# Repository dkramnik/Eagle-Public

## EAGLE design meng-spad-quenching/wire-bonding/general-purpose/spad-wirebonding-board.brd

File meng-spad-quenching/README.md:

#meng-spad-quenching

This repository contains circuit designs for my M.Eng. project in Professor Rajeev Ram's group at MIT. These circuits are primarily related to quenching single-photon avalanche diodes (SPADs) fabricated in 90nm CMOS through MOSIS. My thesis contains full documentation (dspace link posted when available).

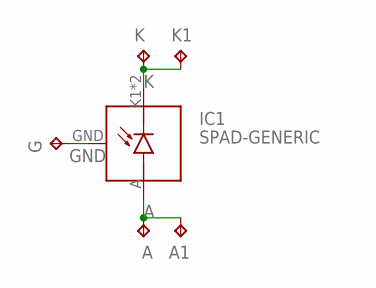
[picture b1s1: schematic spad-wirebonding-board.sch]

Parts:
A, A1: TPTP10R; TP10R
G: TPTP10R; TP10R
IC1: SPAD-GENERIC; SPAD-WIREBOND-GENERIC-CRYO
K, K1: TPTP10R; TP10R

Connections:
A: A.TP, A1.TP, IC1.A (SPAD_ANODE)
GND: G.TP, IC1.GND
K: IC1.K1 (SPAD_CATHODE), IC1.K2 (SPAD_CATHODE), K.TP, K1.TP

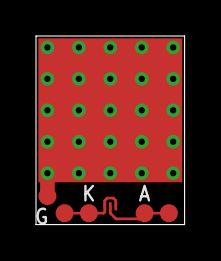
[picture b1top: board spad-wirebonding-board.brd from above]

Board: 2 copper layers, 8.3 x 10.5 mm, 6 parts (0 on the bottom side), 3 nets.

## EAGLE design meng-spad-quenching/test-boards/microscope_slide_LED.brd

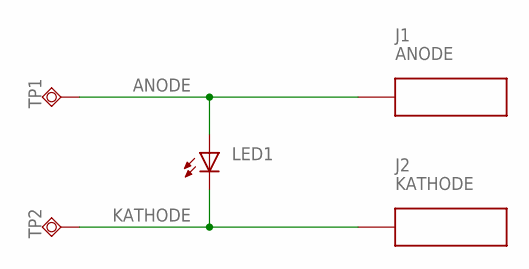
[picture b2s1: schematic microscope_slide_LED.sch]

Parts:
J1: ANODE; 0.125_PAD
J2: KATHODE; 0.125_PAD
LED1: LEDCHIPLED_0603; CHIPLED_0603
TP1: ANODE; TP20SQ
TP2: KATHODE; TP20SQ

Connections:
ANODE: J1.1, LED1.A, TP1.TP
KATHODE: J2.1, LED1.C, TP2.TP

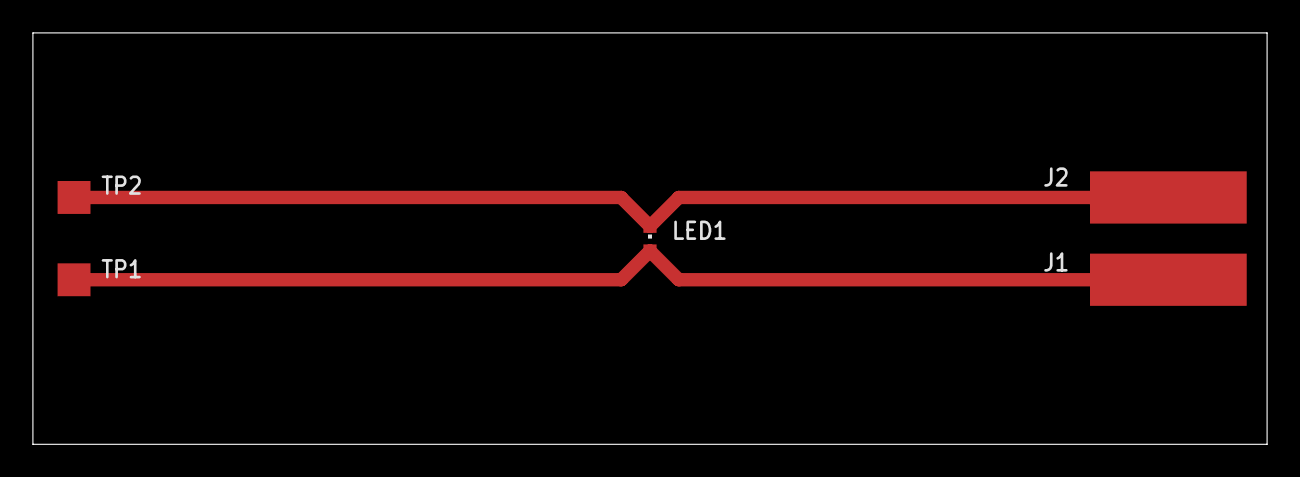
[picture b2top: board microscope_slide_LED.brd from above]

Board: 2 copper layers, 75.0 x 25.0 mm, 5 parts (0 on the bottom side), 2 nets.

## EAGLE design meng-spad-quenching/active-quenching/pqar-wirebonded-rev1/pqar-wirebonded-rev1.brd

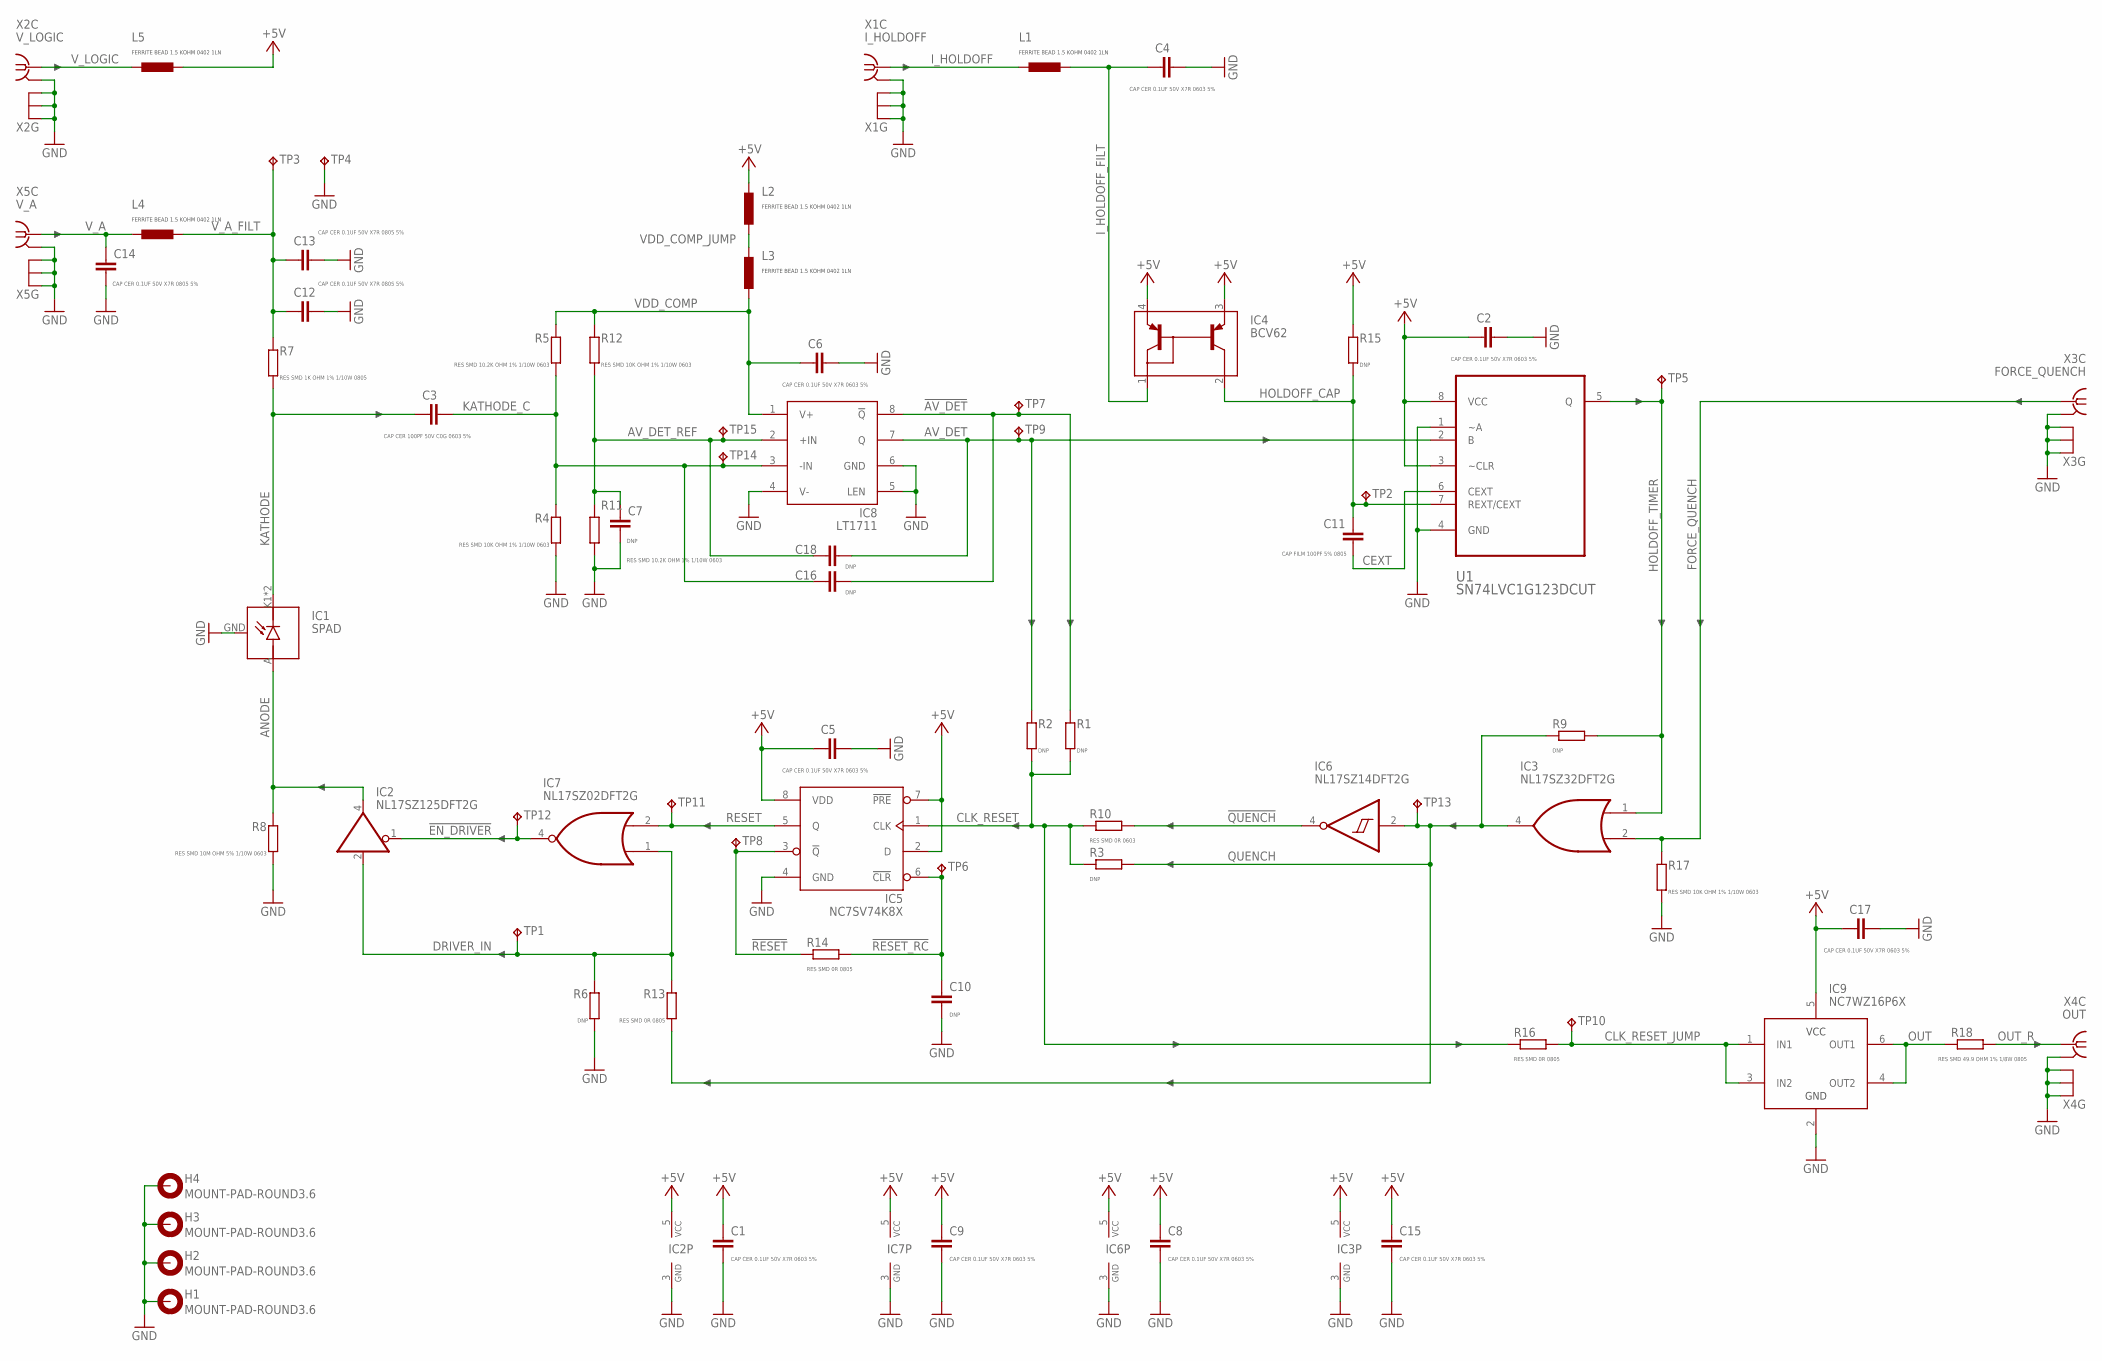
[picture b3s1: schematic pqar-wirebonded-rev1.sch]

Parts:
C1, C2, C4, C5, C6, C8, C9, C15, C17: CAP CER 0.1UF 50V X7R 0603 5%; C0603
C3: CAP CER 100PF 50V C0G 0603 5%; C0603
C7: DNP; C0603
C10, C16, C18: DNP; C0805
C11: CAP FILM 100PF 5% 0805; C0805
C12, C13, C14: CAP CER 0.1UF 50V X7R 0805 5%; C0805
H1, H2, H3, H4: MOUNT-PAD-ROUND3.6; 3,6-PAD
IC1: SPAD; SPAD-WIREBOND-GENERIC-CRYO
IC2: NL17SZ125DFT2G; SC70-5
IC3: NL17SZ32DFT2G; SC70-5
IC4: BCV62; SOT143B
IC5: NC7SV74K8X; US8_3.1MM_JDEC_MO-187
IC6: NL17SZ14DFT2G; SC70-5
IC7: NL17SZ02DFT2G; SC70-5
IC8: LT1711; MSOP8
IC9: NC7WZ16P6X; SC70-6L
L1, L2, L3, L4, L5: FERRITE BEAD 1.5 KOHM 0402 1LN; R0402
R1, R2, R6, R15: DNP; R0805
R3, R9: DNP; R0603
R4, R12, R17: RES SMD 10K OHM 1% 1/10W 0603; R0603
R5, R11: RES SMD 10.2K OHM 1% 1/10W 0603; R0603
R7: RES SMD 1K OHM 1% 1/10W 0805; R0805
R8: RES SMD 10M OHM 5% 1/10W 0603; R0603
R10: RES SMD 0R 0603; R0603
R13, R14, R16: RES SMD 0R 0805; R0805
R18: RES SMD 49.9 OHM 1% 1/8W 0805; R0805
TP1, TP2, TP3, TP4, TP5, TP6, TP7, TP8, TP9, TP10, TP11, TP12, TP13, TP14, TP15: AV_DET; TP10R
U1: SN74LVC1G123DCUT; SOP50P310X90-8N
X1: I_HOLDOFF; MMCX-SMT-BIGPADS
X2: V_LOGIC; MMCX-SMT-BIGPADS
X3: FORCE_QUENCH; MMCX-SMT-BIGPADS
X4: OUT; MMCX-SMT-BIGPADS
X5: V_A; MMCX-SMT-BIGPADS

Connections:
!AV_DET: C16.2, IC8.8 (!Q), R1.1, TP7.TP
!EN_DRIVER: IC2.1 (OE), IC7.4 (O), TP12.TP
!QUENCH: IC6.4 (O), R10.2
!RESET: IC5.3 (!Q), R14.1, TP8.TP
!RESET_RC: C10.1, IC5.6 (!CLR), R14.2, TP6.TP
+5V: C1.1, C2.1, C5.1, C8.1, C9.1, C15.1, C17.1, IC2.5 (VCC), IC3.5 (VCC), IC4.3 (E_OUT), IC4.4 (E_IN), IC5.2 (D), IC5.7 (!PRE), IC5.8 (VDD), IC6.5 (VCC), IC7.5 (VCC), IC9.5 (VCC), L2.1, L5.2, R15.1, U1.3 (~CLR), U1.8 (VCC)
ANODE: IC1.A (SPAD_ANODE), IC2.4 (O), R8.1
AV_DET: C18.2, IC8.7 (Q), R2.1, TP9.TP, U1.2 (B)
AV_DET_REF: C7.1, C18.1, IC8.2 (+IN), R11.1, R12.2, TP15.TP
CEXT: C11.2, U1.6 (CEXT)
CLK_RESET: IC5.1 (CLK), R1.2, R2.2, R3.1, R10.1, R16.1
CLK_RESET_JUMP: IC9.1 (IN1), IC9.3 (IN2), R16.2, TP10.TP
DRIVER_IN: IC2.2 (I), IC7.1 (I0), R6.1, R13.1, TP1.TP
FORCE_QUENCH: IC3.2 (I1), R17.1, X3.S (1)
GND: C1.2, C2.2, C4.2, C5.2, C6.2, C7.2, C8.2, C9.2, C10.2, C12.2, C13.2, C14.2, C15.2, C17.2, H1.B3,6, H2.B3,6, H3.B3,6, H4.B3,6, IC1.GND, IC2.3 (GND), IC3.3 (GND), IC5.4 (GND), IC6.3 (GND), IC7.3 (GND), IC8.4 (V-), IC8.5 (LEN), IC8.6 (GND), IC9.2 (GND), R4.2, R6.2, R8.2, R11.2, R17.2, TP4.TP, U1.1 (~A), U1.4 (GND), X1.G1 (GND), X1.G2 (GND), X1.G3 (GND), X1.G4 (GND), X2.G1 (GND), X2.G2 (GND), X2.G3 (GND), X2.G4 (GND), X3.G1 (GND), X3.G2 (GND), X3.G3 (GND), X3.G4 (GND), X4.G1 (GND), X4.G2 (GND), X4.G3 (GND), X4.G4 (GND), X5.G1 (GND), X5.G2 (GND), X5.G3 (GND), X5.G4 (GND)
HOLDOFF_CAP: C11.1, IC4.2 (C_OUT), R15.2, TP2.TP, U1.7 (REXT/CEXT)
HOLDOFF_TIMER: IC3.1 (I0), R9.2, TP5.TP, U1.5 (Q)
I_HOLDOFF: L1.1, X1.S (1)
I_HOLDOFF_FILT: C4.1, IC4.1 (BC_IN), L1.2
KATHODE: C3.1, IC1.K1 (SPAD_CATHODE), IC1.K2 (SPAD_CATHODE), R7.2
KATHODE_C: C3.2, C16.1, IC8.3 (-IN), R4.1, R5.2, TP14.TP
OUT: IC9.4 (OUT2), IC9.6 (OUT1), R18.2
OUT_R: R18.1, X4.S (1)
QUENCH: IC3.4 (O), IC6.2 (I), R3.2, R9.1, R13.2, TP13.TP
RESET: IC5.5 (Q), IC7.2 (I1), TP11.TP
VDD_COMP: C6.1, IC8.1 (V+), L3.2, R5.1, R12.1
VDD_COMP_JUMP: L2.2, L3.1
V_A: C14.1, L4.1, X5.S (1)
V_A_FILT: C12.1, C13.1, L4.2, R7.1, TP3.TP
V_LOGIC: L5.1, X2.S (1)

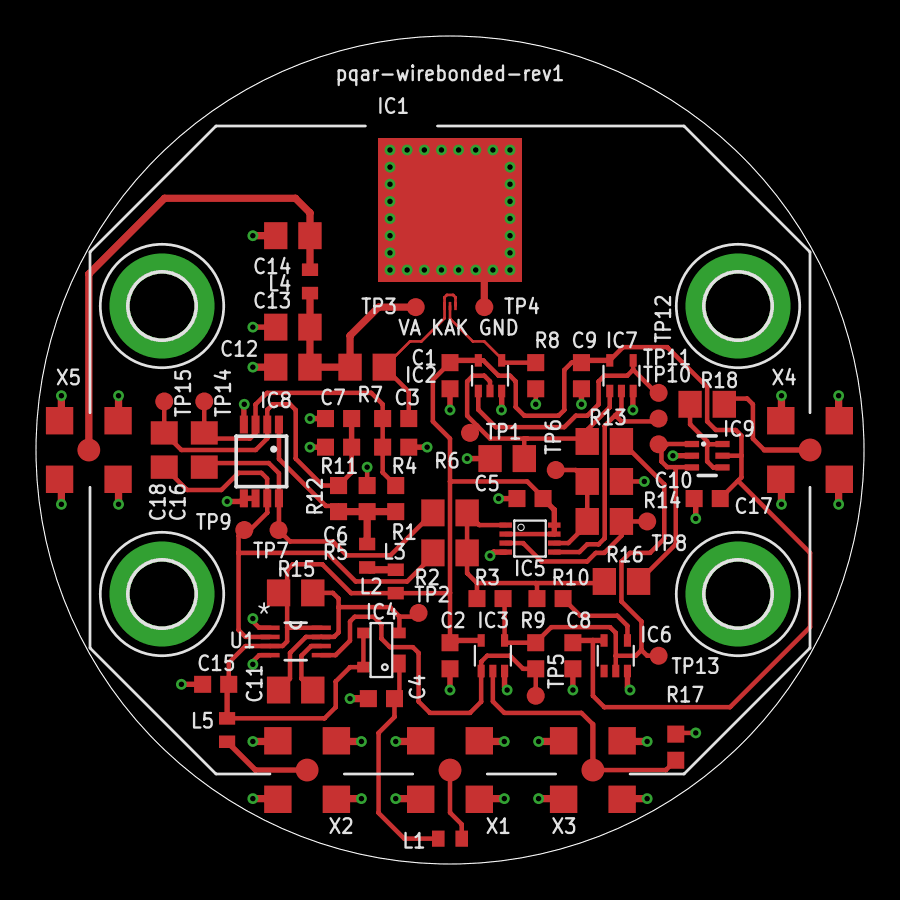
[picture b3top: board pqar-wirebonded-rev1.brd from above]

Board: 2 copper layers, 46.0 x 46.0 mm, 75 parts (0 on the bottom side), 30 nets.

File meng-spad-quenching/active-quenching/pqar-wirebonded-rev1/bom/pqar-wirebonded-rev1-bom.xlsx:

BOM Line | Quantity | DNP | Designators | Value | Package | MFR | MFR P/N | Distributor | Distributor P/N | Distributor Description | Generic Replacement Acceptable | Comments
1 | 9 |  | C1, C2, C4, C5, C6, C8, C9, C15, C17 | CAP CER 0.1UF 50V X7R 0603 5% | C0603 |  |  |  |  |  | Yes
2 | 3 | DNP | C10, C16, C18 | DNP | C0805 |  |  |  |  |  | N/A
3 | 1 |  | C11 | CAP FILM 100PF 5% 0805 | C0805 |  |  |  |  |  | Yes
4 | 3 |  | C12, C13, C14 | CAP CER 0.1UF 50V X7R 0805 5% | C0805 |  |  |  |  |  | Yes
5 | 1 |  | C3 | CAP CER 100PF 50V C0G 0603 5% | C0603 |  |  |  |  |  | Yes
6 | 1 | DNP | C7 | DNP | C0603
7 | 4 | DNP | H1, H2, H3, H4 | Mounting Hole | Custom
8 | 1 | DNP | IC1 | Bare Die | Custom
9 | 1 |  | IC2 | NL17SZ125DFT2G | SC70-5 | ON Semiconductor | NL17SZ125DFT2G | Digikey | NL17SZ125DFT2GOSTR-ND | IC BUFFER NON-INVERT 5.5V SC88A | No
10 | 1 |  | IC3 | NL17SZ32DFT2G | SC70-5 | ON Semiconductor | NL17SZ32DFT2G | Digikey | NL17SZ32DFT2GOSTR-ND | IC GATE OR 1CH 2-INP SC88A | No
11 | 1 |  | IC4 | BCV62 | SOT143B | Infineon Technologies | BCV62 | Digikey | BCV62AE6327HTSA1TR-ND | TRANS 2PNP 30V 0.1A SOT143 | No
12 | 1 |  | IC5 | NC7SV74K8X | US8 | ON Semiconductor | NC7SV74K8X | Digikey | NC7SV74K8XTR-ND | IC FF D-TYPE SNGL 1BIT US8 | No
13 | 1 |  | IC6 | NL17SZ14DFT2G | SC70-5 | ON Semiconductor | NL17SZ14DFT2G | Digikey | NL17SZ14DFT2GOSTR-ND | IC INVERTER SCHMITT 1CH SC88A | No
14 | 1 |  | IC7 | NL17SZ02DFT2G | SC70-5 | ON Semiconductor | NL17SZ02DFT2G | Digikey | NL17SZ02DFT2GOSTR-ND | IC GATE NOR 1CH 2-INP SC88A | No
15 | 1 |  | IC8 | LT1711 | MSOP8 | Analog Devices Inc. | LT1711CMS8#PBF | Digikey | LT1711CMS8#PBF-ND | IC COMP R-RINOUT SINGLE 8-MSOP | No
16 | 1 |  | IC9 | NC7WZ16P6X | SC70-6L | ON Semiconductor | NC7WZ16P6X | Digikey | NC7WZ16P6XTR-ND | IC BUFFER NON-INVERT 5.5V SC88 | No
17 | 5 |  | L1, L2, L3, L4, L5 | FERRITE BEAD 1.5 KOHM 0402 1LN | R0402 | TDK Corporation | MMZ1005Y152CT000 | Digikey | 445-2158-2-ND | FERRITE BEAD 1.5 KOHM 0402 1LN | Yes | MPN is example
18 | 4 | DNP | R1, R2, R6, R15 | DNP | R0805
19 | 1 |  | R10 | RES SMD 0R 0603 | R0603 |  |  |  |  |  | Yes
20 | 3 |  | R13, R14, R16 | RES SMD 0R 0805 | R0805 |  |  |  |  |  | Yes
21 | 1 |  | R18 | RES SMD 49.9 OHM 1% 1/8W 0805 | R0805 |  |  |  |  |  | Yes
22 | 2 | DNP | R3, R9 | DNP | R0603
23 | 3 |  | R4, R12, R17 | RES SMD 10K OHM 1% 1/10W 0603 | R0603 |  |  |  |  |  | Yes
24 | 2 |  | R5, R11 | RES SMD 10.2K OHM 1% 1/10W 0603 | R0603 |  |  |  |  |  | Yes
25 | 1 |  | R7 | RES SMD 1K OHM 1% 1/10W 0805 | R0805 |  |  |  |  |  | Yes
26 | 1 |  | R8 | RES SMD 10M OHM 5% 1/10W 0603 | R0603 |  |  |  |  |  | Yes
27 | 15 | DNP | TP1 through TP15 | N/A | TP10R
28 | 1 |  | U1 | SN74LVC1G123DCUT | 8VSSOP | Texas Instruments | SN74LVC1G123DCUT | Digikey | 296-26594-2-ND | IC MULTIVIBRATOR 18.5NS 8VSSOP | No
29 | 1 |  | X1, X2, X3, X4, X5 | Various | MMCX-SMT | Molex | 734152063 | Digikey | WM3914TR-ND | CONN MMCX JACK STR 50 OHM SMD | No

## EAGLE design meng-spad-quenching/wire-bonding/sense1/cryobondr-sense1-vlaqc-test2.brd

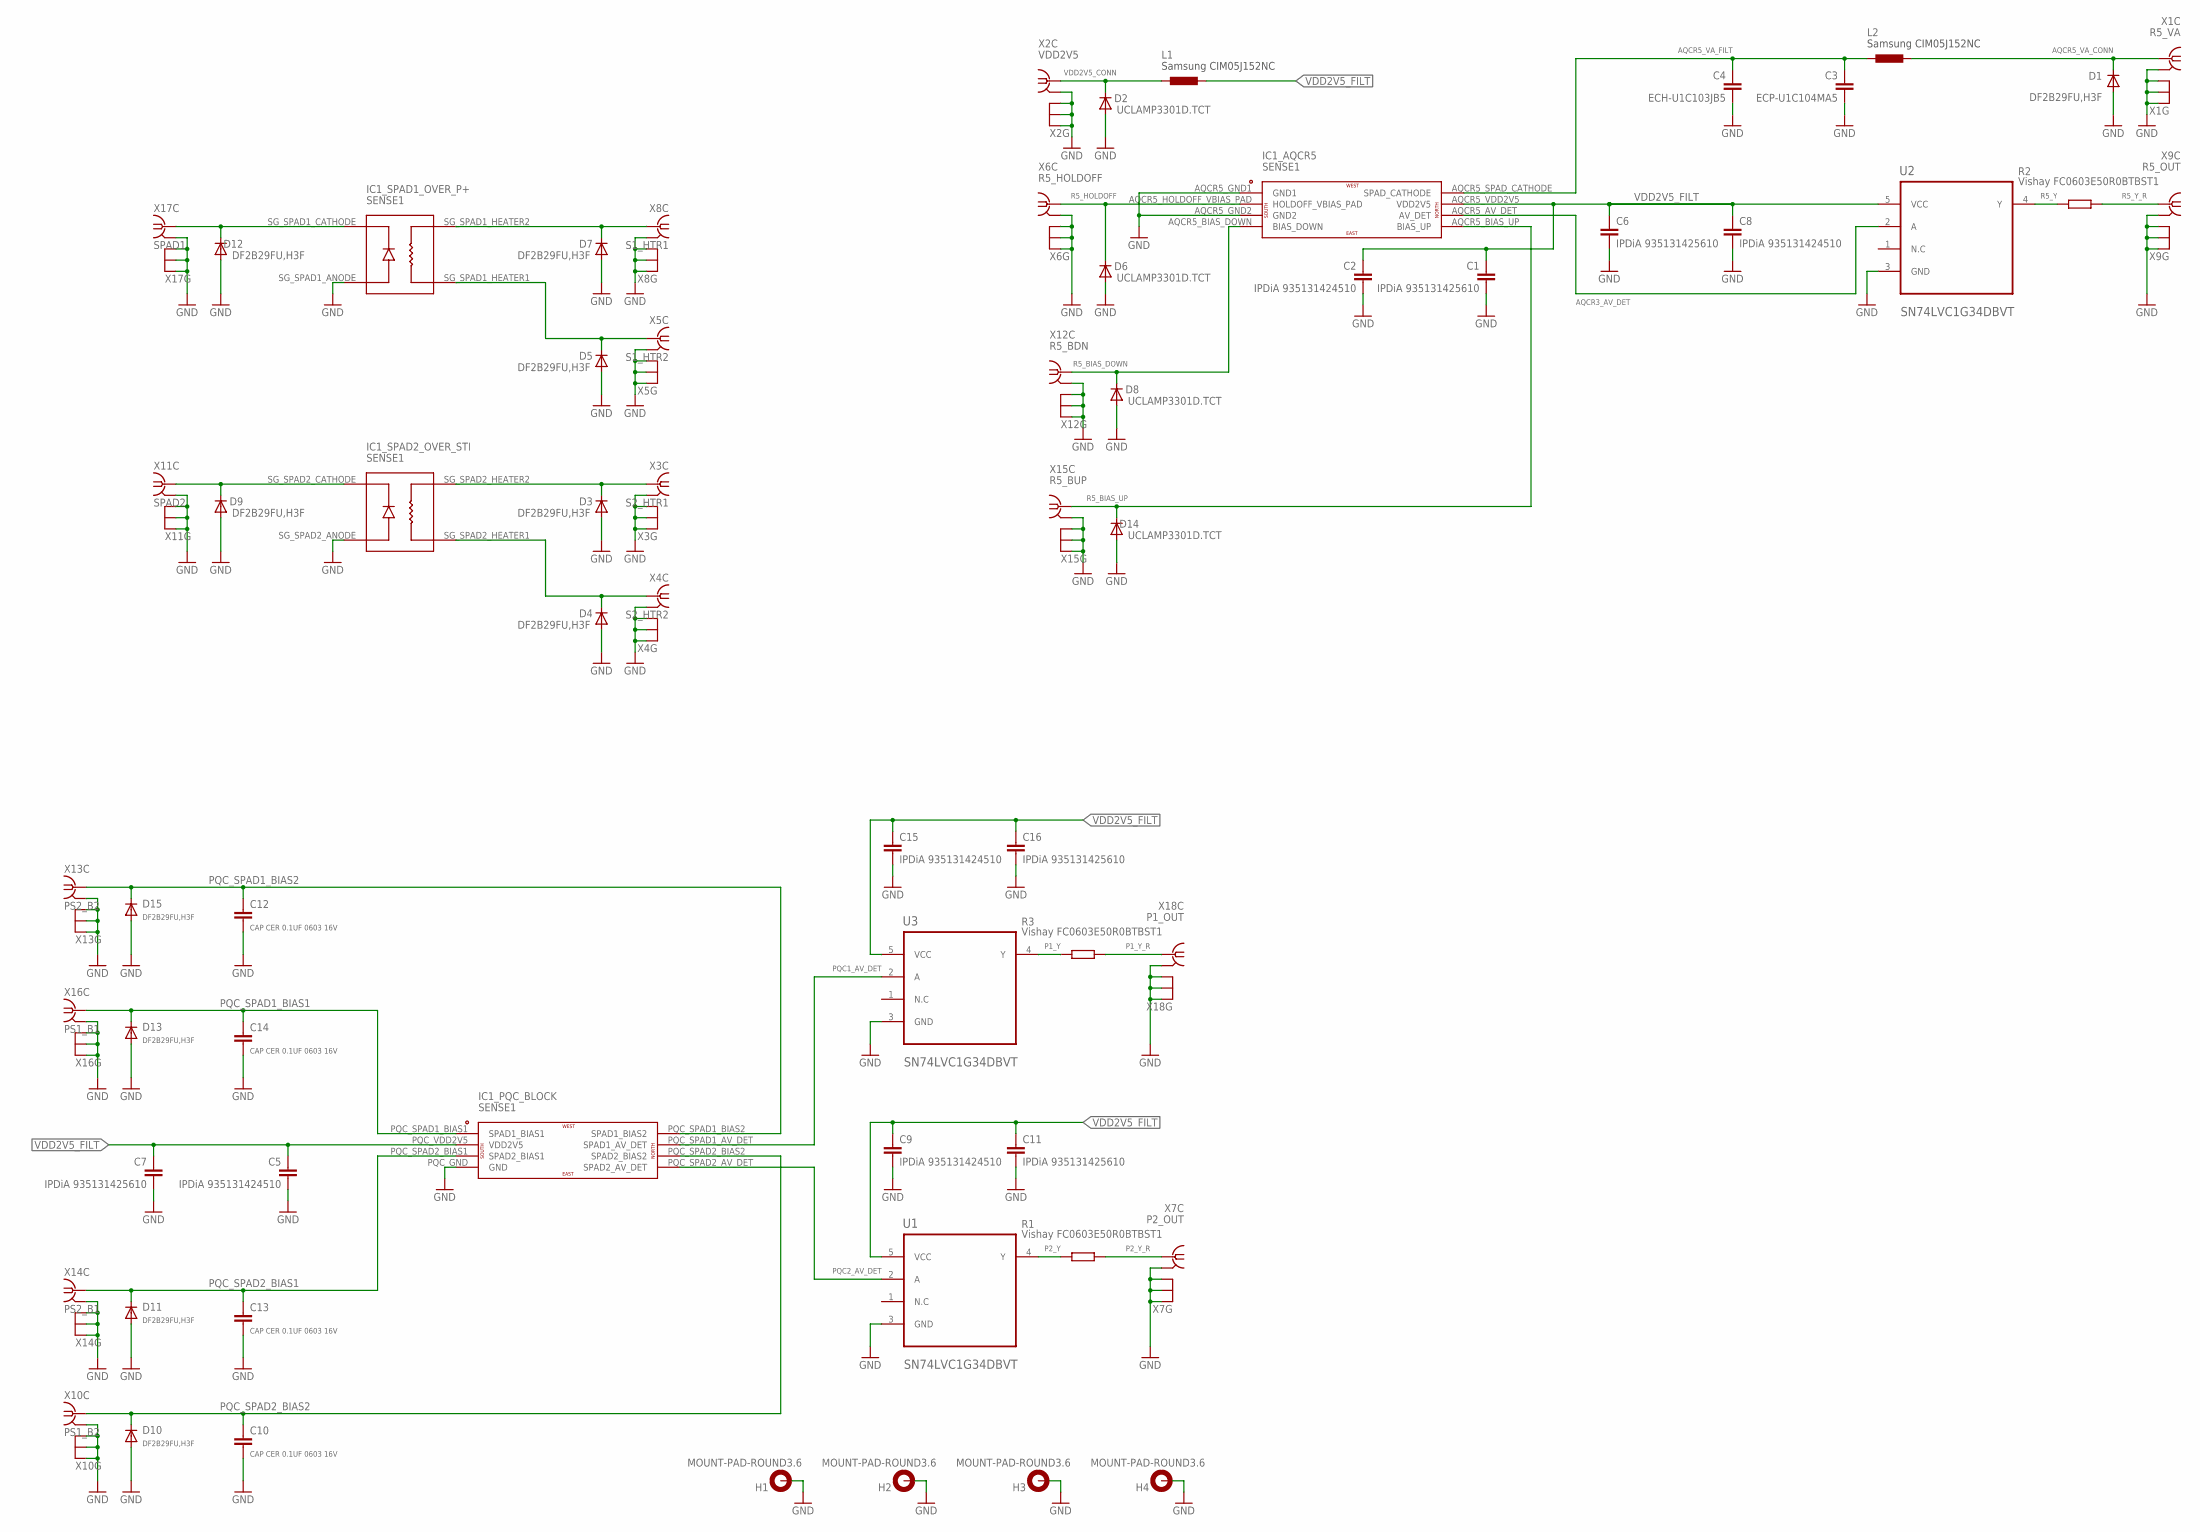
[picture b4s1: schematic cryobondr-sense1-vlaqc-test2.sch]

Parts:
C1, C6, C7, C11, C16: IPDiA 935131425610; C0603
C2, C5, C8, C9, C15: IPDiA 935131424510; C0402
C3: ECP-U1C104MA5; C0805
C4: ECH-U1C103JB5; C0805
C10, C12, C13, C14: CAP CER 0.1UF 0603 16V; C0603
D1, D3, D4, D5, D7, D9, D10, D11, D12, D13, D15: DF2B29FU,H3F; SOD323-R
D2, D6, D8, D14: UCLAMP3301D.TCT; SOD323-R
H1, H2, H3, H4: MOUNT-PAD-ROUND3.6; 3,6-PAD
IC1: SENSE1; SENSE1-WIREBOND-VLAQC-TEST2
L1, L2: Samsung CIM05J152NC; R0402
R1, R2, R3: Vishay FC0603E50R0BTBST1; R0603
U1, U2, U3: SN74LVC1G34DBVT; SOT95P280X145-5N
X1: R5_VA; MMCX-SMT-BIGPADS
X2: VDD2V5; MMCX-SMT-BIGPADS
X3: S2_HTR1; MMCX-SMT-BIGPADS
X4: S2_HTR2; MMCX-SMT-BIGPADS
X5: S1_HTR2; MMCX-SMT-BIGPADS
X6: R5_HOLDOFF; MMCX-SMT-BIGPADS
X7: P2_OUT; MMCX-SMT-BIGPADS
X8: S1_HTR1; MMCX-SMT-BIGPADS
X9: R5_OUT; MMCX-SMT-BIGPADS
X10: PS1_B2; MMCX-SMT-BIGPADS
X11: SPAD2; MMCX-SMT-BIGPADS
X12: R5_BDN; MMCX-SMT-BIGPADS
X13: PS2_B2; MMCX-SMT-BIGPADS
X14: PS2_B1; MMCX-SMT-BIGPADS
X15: R5_BUP; MMCX-SMT-BIGPADS
X16: PS1_B1; MMCX-SMT-BIGPADS
X17: SPAD1; MMCX-SMT-BIGPADS
X18: P1_OUT; MMCX-SMT-BIGPADS

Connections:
AQCR3_AV_DET: IC1.AQCR5_AV_DET (AV_DET), U2.2 (A)
AQCR5_VA_CONN: D1.C, L2.2, X1.S (1)
AQCR5_VA_FILT: C3.1, C4.1, IC1.AQCR5_SPAD_CATHODE (SPAD_CATHODE), L2.1
GND: C1.2, C2.2, C3.2, C4.2, C5.2, C6.2, C7.2, C8.2, C9.2, C10.2, C11.2, C12.2, C13.2, C14.2, C15.2, C16.2, D1.A, D2.A, D3.A, D4.A, D5.A, D6.A, D7.A, D8.A, D9.A, D10.A, D11.A, D12.A, D13.A, D14.A, D15.A, H1.B3,6, H2.B3,6, H3.B3,6, H4.B3,6, IC1.AQCR5_GND1 (GND1), IC1.AQCR5_GND2 (GND2), IC1.PQC_GND (GND), IC1.SG_SPAD1_ANODE (SPAD_ANODE), IC1.SG_SPAD2_ANODE (SPAD_ANODE), U1.3 (GND), U2.3 (GND), U3.3 (GND), X1.G1 (GND), X1.G2 (GND), X1.G3 (GND), X1.G4 (GND), X2.G1 (GND), X2.G2 (GND), X2.G3 (GND), X2.G4 (GND), X3.G1 (GND), X3.G2 (GND), X3.G3 (GND), X3.G4 (GND), X4.G1 (GND), X4.G2 (GND), X4.G3 (GND), X4.G4 (GND), X5.G1 (GND), X5.G2 (GND), X5.G3 (GND), X5.G4 (GND), X6.G1 (GND), X6.G2 (GND), X6.G3 (GND), X6.G4 (GND), X7.G1 (GND), X7.G2 (GND), X7.G3 (GND), X7.G4 (GND), X8.G1 (GND), X8.G2 (GND), X8.G3 (GND), X8.G4 (GND), X9.G1 (GND), X9.G2 (GND), X9.G3 (GND), X9.G4 (GND), X10.G1 (GND), X10.G2 (GND), X10.G3 (GND), X10.G4 (GND), X11.G1 (GND), X11.G2 (GND), X11.G3 (GND), X11.G4 (GND), X12.G1 (GND), X12.G2 (GND), X12.G3 (GND), X12.G4 (GND), X13.G1 (GND), X13.G2 (GND), X13.G3 (GND), X13.G4 (GND), X14.G1 (GND), X14.G2 (GND), X14.G3 (GND), X14.G4 (GND), X15.G1 (GND), X15.G2 (GND), X15.G3 (GND), X15.G4 (GND), X16.G1 (GND), X16.G2 (GND), X16.G3 (GND), X16.G4 (GND), X17.G1 (GND), X17.G2 (GND), X17.G3 (GND), X17.G4 (GND), X18.G1 (GND), X18.G2 (GND), X18.G3 (GND), X18.G4 (GND)
P1_Y: R3.1, U3.4 (Y)
P1_Y_R: R3.2, X18.S (1)
P2_Y: R1.1, U1.4 (Y)
P2_Y_R: R1.2, X7.S (1)
PQC1_AV_DET: IC1.PQC_SPAD1_AV_DET (SPAD1_AV_DET), U3.2 (A)
PQC2_AV_DET: IC1.PQC_SPAD2_AV_DET (SPAD2_AV_DET), U1.2 (A)
PQC_SPAD1_BIAS1: C14.1, D13.C, IC1.PQC_SPAD1_BIAS1 (SPAD1_BIAS1), X16.S (1)
PQC_SPAD1_BIAS2: C12.1, D15.C, IC1.PQC_SPAD1_BIAS2 (SPAD1_BIAS2), X13.S (1)
PQC_SPAD2_BIAS1: C13.1, D11.C, IC1.PQC_SPAD2_BIAS1 (SPAD2_BIAS1), X14.S (1)
PQC_SPAD2_BIAS2: C10.1, D10.C, IC1.PQC_SPAD2_BIAS2 (SPAD2_BIAS2), X10.S (1)
R5_BIAS_DOWN: D8.C, IC1.AQCR5_BIAS_DOWN (BIAS_DOWN), X12.S (1)
R5_BIAS_UP: D14.C, IC1.AQCR5_BIAS_UP (BIAS_UP), X15.S (1)
R5_HOLDOFF: D6.C, IC1.AQCR5_HOLDOFF_VBIAS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 (HOLDOFF_VBIAS_PAD), X6.S (1)
R5_Y: R2.1, U2.4 (Y)
R5_Y_R: R2.2, X9.S (1)
SPAD1_CATH: D12.C, IC1.SG_SPAD1_CATHODE (SPAD_CATHODE), X17.S (1)
SPAD1_HTR: D7.C, IC1.SG_SPAD1_HEATER2 (SPAD_HEATER2), X8.S (1)
SPAD1_HTR1: D3.C, IC1.SG_SPAD2_HEATER2 (SPAD_HEATER2), X3.S (1)
SPAD2_CATH: D9.C, IC1.SG_SPAD2_CATHODE (SPAD_CATHODE), X11.S (1)
SPAD2_HTR: D5.C, IC1.SG_SPAD1_HEATER1 (SPAD_HEATER1), X5.S (1)
SPAD2_HTR1: D4.C, IC1.SG_SPAD2_HEATER1 (SPAD_HEATER1), X4.S (1)
VDD2V5_CONN: D2.C, L1.1, X2.S (1)
VDD2V5_FILT: C1.1, C2.1, C5.1, C6.1, C7.1, C8.1, C9.1, C11.1, C15.1, C16.1, IC1.AQCR5_VDD2V5 (VDD2V5), IC1.PQC_VDD2V5 (VDD2V5), L1.2, U1.5 (VCC), U2.5 (VCC), U3.5 (VCC)

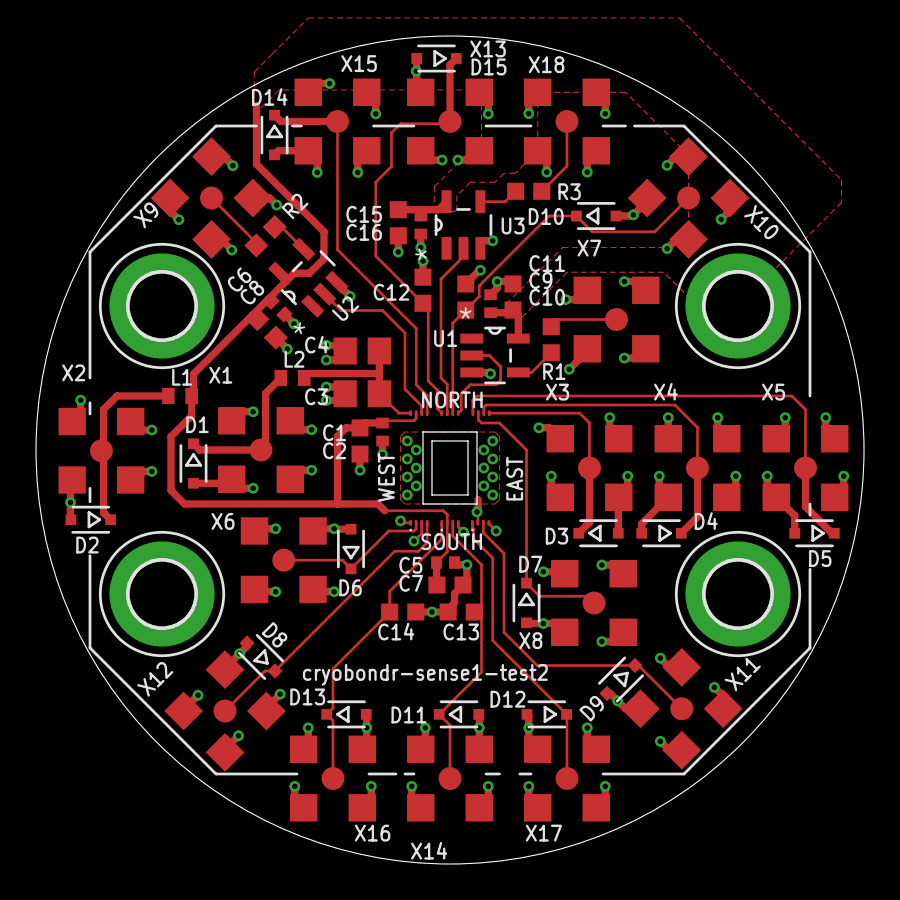
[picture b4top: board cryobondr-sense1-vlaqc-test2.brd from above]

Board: 2 copper layers, 46.0 x 46.0 mm, 62 parts (0 on the bottom side), 27 nets.

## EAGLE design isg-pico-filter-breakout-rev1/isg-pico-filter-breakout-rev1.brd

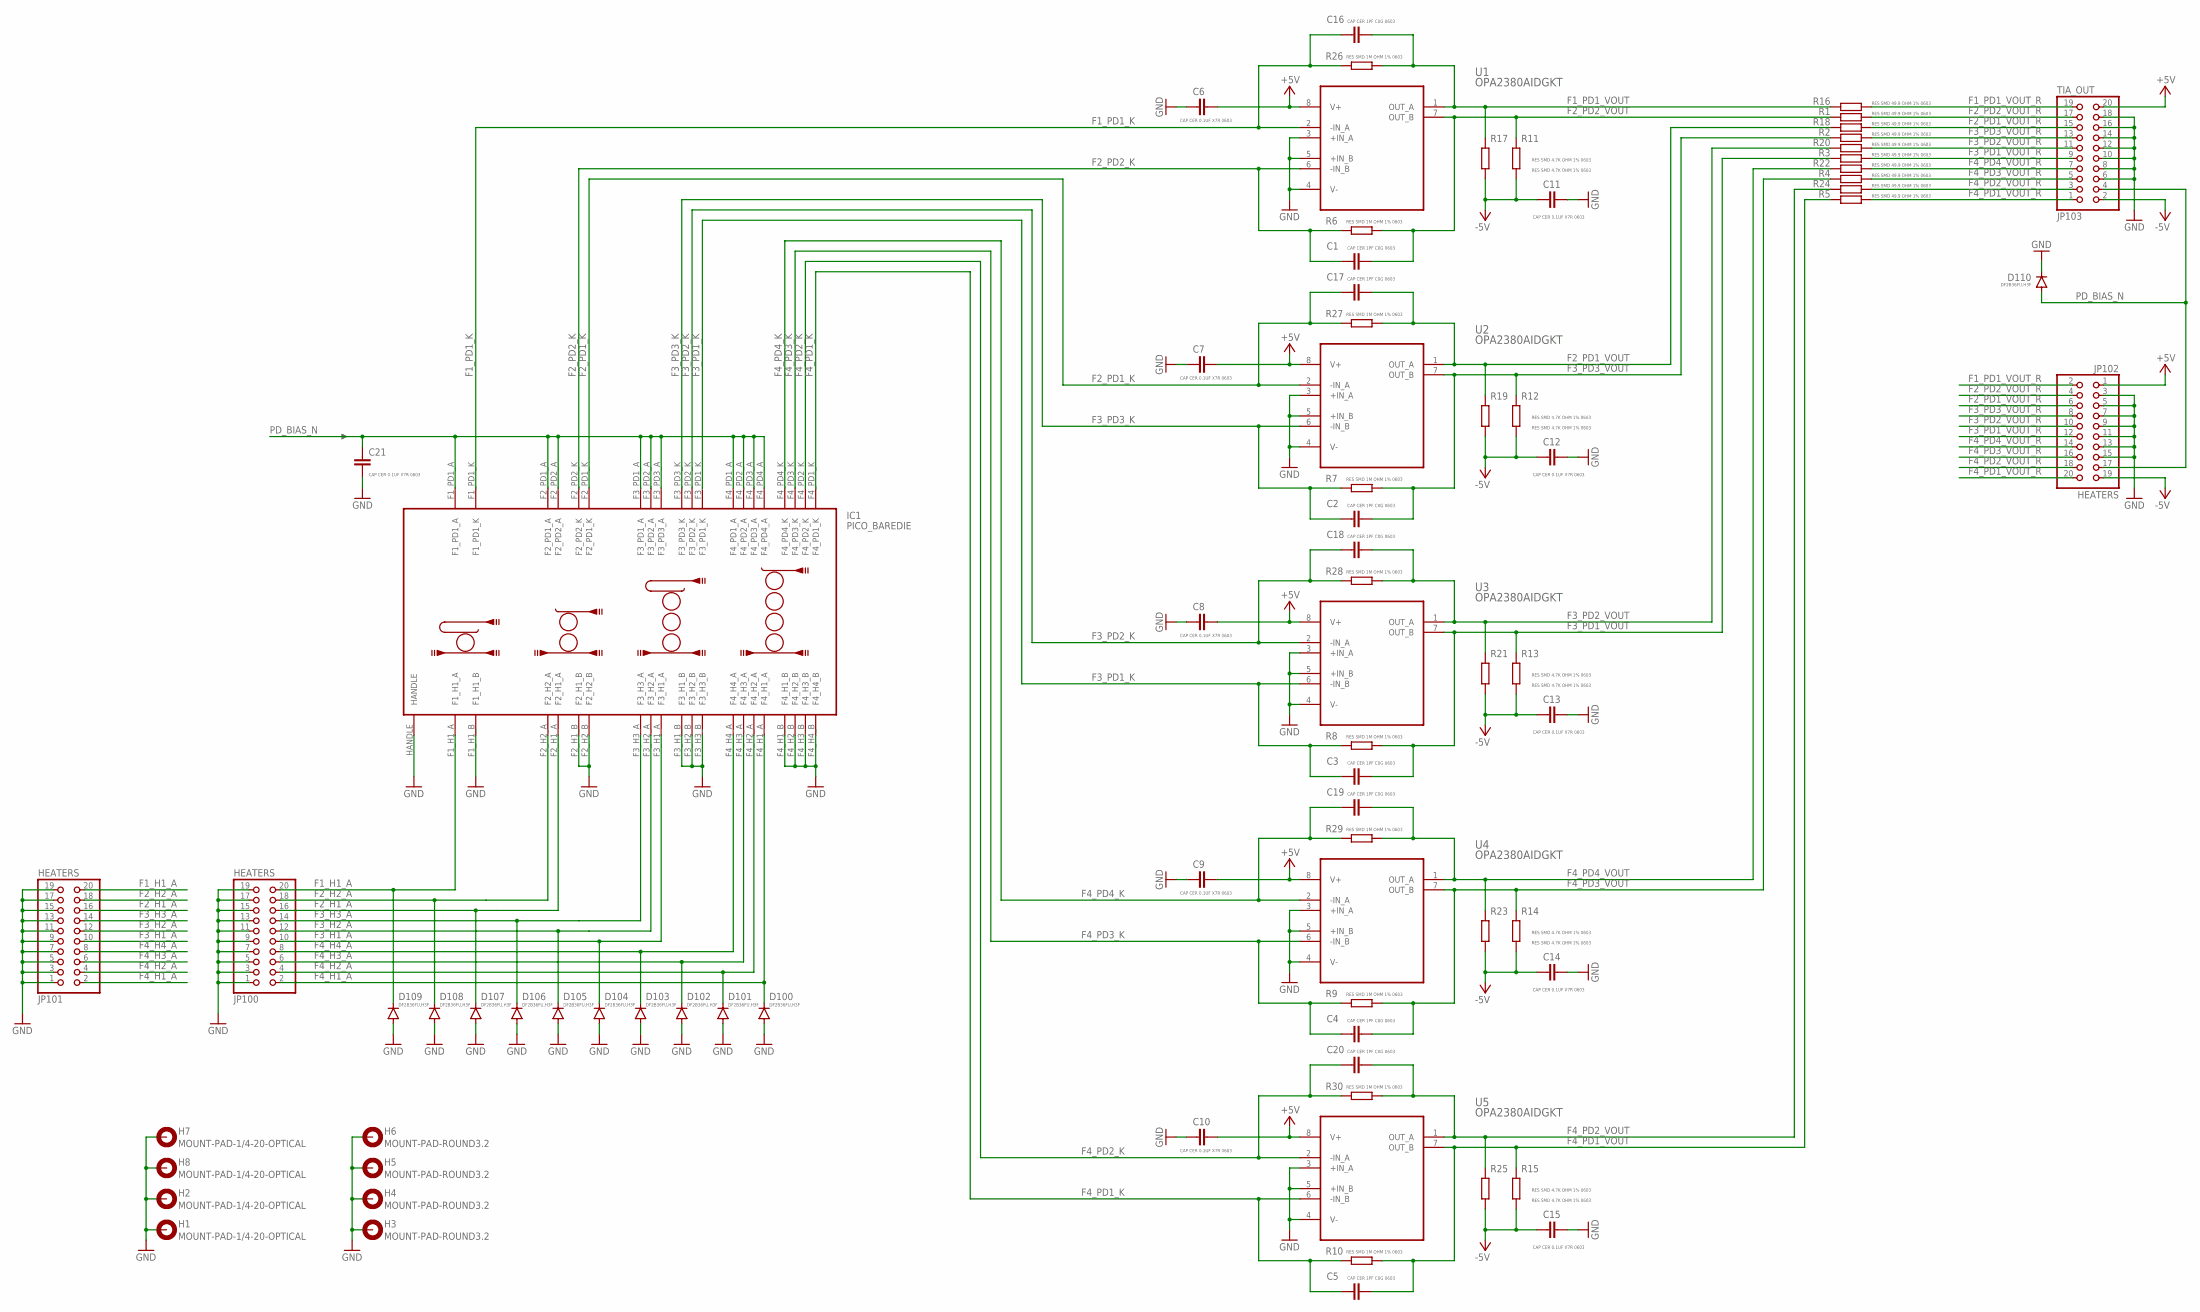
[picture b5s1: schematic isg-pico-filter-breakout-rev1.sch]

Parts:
C1, C2, C3, C4, C5, C16, C17, C18, C19, C20: CAP CER 1PF C0G 0603; C0603
C6, C7, C8, C9, C10, C11, C12, C13, C14, C15, C21: CAP CER 0.1UF X7R 0603; C0603
D100, D101, D102, D103, D104, D105, D106, D107, D108, D109, D110: DF2B36FU,H3F; SOD323-W
H1, H2, H7, H8: MOUNT-PAD-1/4-20-OPTICAL; MOUNT-PAD-1/4-20
H3, H4, H5, H6: MOUNT-PAD-ROUND3.2; 3,2-PAD
IC1: PICO_BAREDIE; DIE-PICO-MULTI-RING-FILTERS
JP100: HEATERS; 2X10
JP101, JP102: HEATERS; FTSH-110-01-L-DV-K-TR
JP103: TIA_OUT; 2X10
R1, R2, R3, R4, R5, R16, R18, R20, R22, R24: RES SMD 49.9 OHM 1% 0603; R0603
R6, R7, R8, R9, R10, R26, R27, R28, R29, R30: RES SMD 1M OHM 1% 0603; R0603
R11, R12, R13, R14, R15, R17, R19, R21, R23, R25: RES SMD 4.7K OHM 1% 0603; R0603
U1, U2, U3, U4, U5: OPA2380AIDGKT; SOP65P490X110-8N

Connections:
+5V: C6.1, C7.1, C8.1, C9.1, C10.1, JP102.1, JP103.20, U1.8 (V+), U2.8 (V+), U3.8 (V+), U4.8 (V+), U5.8 (V+)
-5V: C11.2, C12.2, C13.2, C14.2, C15.2, JP102.19, JP103.2, R11.2, R12.2, R13.2, R14.2, R15.2, R17.2, R19.2, R21.2, R23.2, R25.2
F1_H1_A: D109.C, IC1.F1_H1_A, JP100.20, JP101.20
F1_PD1_K: C16.1, IC1.F1_PD1_K, R26.1, U1.2 (-IN_A)
F1_PD1_VOUT: C16.2, R16.1, R17.1, R26.2, U1.1 (OUT_A)
F1_PD1_VOUT_R: JP102.2, JP103.19, R16.2
F2_H1_A: D107.C, IC1.F2_H1_A, JP100.16, JP101.16
F2_H2_A: D108.C, IC1.F2_H2_A, JP100.18, JP101.18
F2_PD1_K: C17.1, IC1.F2_PD1_K, R27.1, U2.2 (-IN_A)
F2_PD1_VOUT: C17.2, R18.1, R19.1, R27.2, U2.1 (OUT_A)
F2_PD1_VOUT_R: JP102.6, JP103.15, R18.2
F2_PD2_K: C1.1, IC1.F2_PD2_K, R6.1, U1.6 (-IN_B)
F2_PD2_VOUT: C1.2, R1.1, R6.2, R11.1, U1.7 (OUT_B)
F2_PD2_VOUT_R: JP102.4, JP103.17, R1.2
F3_H1_A: D104.C, IC1.F3_H1_A, JP100.10, JP101.10
F3_H2_A: D105.C, IC1.F3_H2_A, JP100.12, JP101.12
F3_H3_A: D106.C, IC1.F3_H3_A, JP100.14, JP101.14
F3_PD1_K: C3.1, IC1.F3_PD1_K, R8.1, U3.6 (-IN_B)
F3_PD1_VOUT: C3.2, R3.1, R8.2, R13.1, U3.7 (OUT_B)
F3_PD1_VOUT_R: JP102.12, JP103.9, R3.2
F3_PD2_K: C18.1, IC1.F3_PD2_K, R28.1, U3.2 (-IN_A)
F3_PD2_VOUT: C18.2, R20.1, R21.1, R28.2, U3.1 (OUT_A)
F3_PD2_VOUT_R: JP102.10, JP103.11, R20.2
F3_PD3_K: C2.1, IC1.F3_PD3_K, R7.1, U2.6 (-IN_B)
F3_PD3_VOUT: C2.2, R2.1, R7.2, R12.1, U2.7 (OUT_B)
F3_PD3_VOUT_R: JP102.8, JP103.13, R2.2
F4_H1_A: D100.C, IC1.F4_H1_A, JP100.2, JP101.2
F4_H2_A: D101.C, IC1.F4_H2_A, JP100.4, JP101.4
F4_H3_A: D102.C, IC1.F4_H3_A, JP100.6, JP101.6
F4_H4_A: D103.C, IC1.F4_H4_A, JP100.8, JP101.8
F4_PD1_K: C5.1, IC1.F4_PD1_K, R10.1, U5.6 (-IN_B)
F4_PD1_VOUT: C5.2, R5.1, R10.2, R15.1, U5.7 (OUT_B)
F4_PD1_VOUT_R: JP102.20, JP103.1, R5.2
F4_PD2_K: C20.1, IC1.F4_PD2_K, R30.1, U5.2 (-IN_A)
F4_PD2_VOUT: C20.2, R24.1, R25.1, R30.2, U5.1 (OUT_A)
F4_PD2_VOUT_R: JP102.18, JP103.3, R24.2
F4_PD3_K: C4.1, IC1.F4_PD3_K, R9.1, U4.6 (-IN_B)
F4_PD3_VOUT: C4.2, R4.1, R9.2, R14.1, U4.7 (OUT_B)
F4_PD3_VOUT_R: JP102.16, JP103.5, R4.2
F4_PD4_K: C19.1, IC1.F4_PD4_K, R29.1, U4.2 (-IN_A)
F4_PD4_VOUT: C19.2, R22.1, R23.1, R29.2, U4.1 (OUT_A)
F4_PD4_VOUT_R: JP102.14, JP103.7, R22.2
GND: C6.2, C7.2, C8.2, C9.2, C10.2, C11.1, C12.1, C13.1, C14.1, C15.1, C21.2, D100.A, D101.A, D102.A, D103.A, D104.A, D105.A, D106.A, D107.A, D108.A, D109.A, D110.C, H1.MOUNT, H2.MOUNT, H3.B3,2, H4.B3,2, H5.B3,2, H6.B3,2, H7.MOUNT, H8.MOUNT, IC1.F1_H1_B, IC1.F2_H1_B, IC1.F2_H2_B, IC1.F3_H1_B, IC1.F3_H2_B, IC1.F3_H3_B, IC1.F4_H1_B, IC1.F4_H2_B, IC1.F4_H3_B, IC1.F4_H4_B, IC1.HANDLE, JP100.1, JP100.3, JP100.5, JP100.7, JP100.9, JP100.11, JP100.13, JP100.15, JP100.17, JP100.19, JP101.1, JP101.3, JP101.5, JP101.7, JP101.9, JP101.11, JP101.13, JP101.15, JP101.17, JP101.19, JP102.3, JP102.5, JP102.7, JP102.9, JP102.11, JP102.13, JP102.15, JP103.6, JP103.8, JP103.10, JP103.12, JP103.14, JP103.16, JP103.18, U1.3 (+IN_A), U1.4 (V-), U1.5 (+IN_B), U2.3 (+IN_A), U2.4 (V-), U2.5 (+IN_B), U3.3 (+IN_A), U3.4 (V-), U3.5 (+IN_B), U4.3 (+IN_A), U4.4 (V-), U4.5 (+IN_B), U5.3 (+IN_A), U5.4 (V-), U5.5 (+IN_B)
PD_BIAS_N: C21.1, D110.A, IC1.F1_PD1_A, IC1.F2_PD1_A, IC1.F2_PD2_A, IC1.F3_PD1_A, IC1.F3_PD2_A, IC1.F3_PD3_A, IC1.F4_PD1_A, IC1.F4_PD2_A, IC1.F4_PD3_A, IC1.F4_PD4_A, JP102.17, JP103.4

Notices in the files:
parts and their libraries:
SparkFun-Connectors: Licensing: Creative Commons ShareAlike 4.0 International - https://creativecommons.org/licenses/by-sa/4.0
microbuilder: This work is placed in the public domain, and may be freely used for commercial and non-commercial work with the following conditions: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
